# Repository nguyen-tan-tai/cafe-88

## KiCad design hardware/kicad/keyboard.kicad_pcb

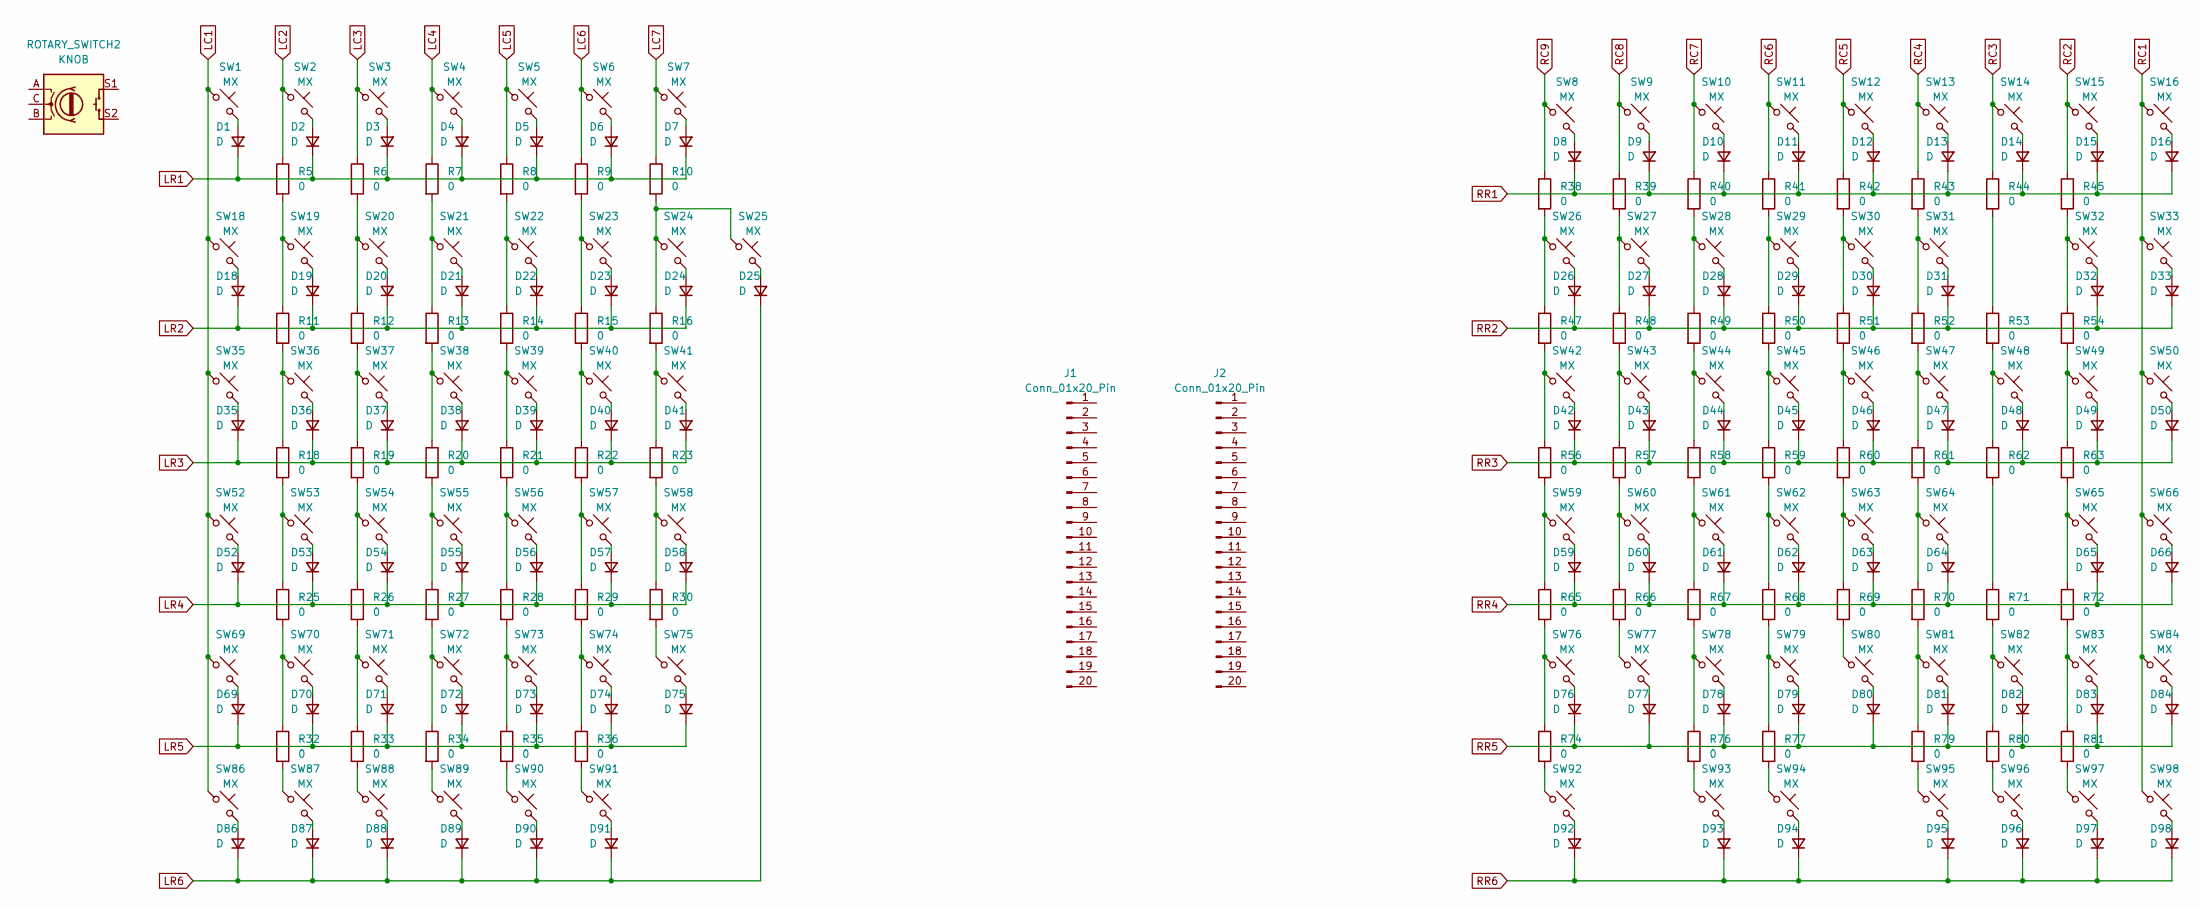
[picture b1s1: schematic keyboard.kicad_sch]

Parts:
D1, D2, D3, D4, D5, D6, D7, D8, D9, D10, D11, D12, D13, D14, D15, D16, D18, D19, D20, D21, D22, D23, D24, D25, D26, D27, D28, D29, D30, D31, D32, D33, D35, D36, D37, D38, D39, D40, D41, D42, D43, D44, D45, D46, D47, D48, D49, D50, D52, D53, D54, D55, D56, D57, D58, D59, D60, D61, D62, D63, D64, D65, D66, D69, D70, D71, D72, D73, D74, D75, D76, D77, D78, D79, D80, D81, D82, D83, D84, D86, D87, D88, D89, D90, D91, D92, D93, D94, D95, D96, D97, D98: D; D_MiniMELF_Handsoldering
J1, J2: Conn_01x20_Pin; PinHeader_1x20_P2.54mm_Vertical
R5, R6, R7, R8, R9, R10, R11, R12, R13, R14, R15, R16, R18, R19, R20, R21, R22, R23, R25, R26, R27, R28, R29, R30, R32, R33, R34, R35, R36, R38, R39, R40, R41, R42, R43, R44, R45, R47, R48, R49, R50, R51, R52, R53, R54, R56, R57, R58, R59, R60, R61, R62, R63, R65, R66, R67, R68, R69, R70, R71, R72, R74, R76, R77, R79, R80, R81: 0; R_2512_6332Metric_Pad1.40x3.35mm_HandSolder
ROTARY_SWITCH2: KNOB; RotaryEncoder_Alps_EC11E-Switch_Vertical_H20mm_CircularMoun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
SW1, SW2, SW3, SW4, SW5, SW6, SW7, SW8, SW9, SW10, SW11, SW12, SW13, SW14, SW15, SW16, SW18, SW19, SW20, SW21, SW22, SW23, SW24, SW25, SW26, SW27, SW28, SW29, SW30, SW31, SW32, SW33, SW35, SW36, SW37, SW38, SW39, SW40, SW41, SW42, SW43, SW44, SW45, SW46, SW47, SW48, SW49, SW50, SW52, SW53, SW54, SW55, SW56, SW57, SW58, SW59, SW60, SW61, SW62, SW63, SW64, SW65, SW66, SW69, SW70, SW71, SW72, SW73, SW74, SW75, SW76, SW77, SW78, SW79, SW80, SW81, SW82, SW83, SW84, SW86, SW87, SW88, SW89, SW90, SW91, SW92, SW93, SW94, SW95, SW96, SW97, SW98: MX; SW_Cherry_MX_1.00u_PCB

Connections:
LC1: SW1.1, SW18.1, SW35.1, SW52.1, SW69.1, SW86.1
LC2: R5.1, SW2.1
LC3: R6.1, SW3.1
LC4: R7.1, SW4.1
LC5: R8.1, SW5.1
LC6: R9.1, SW6.1
LC7: R10.1, SW7.1
LR1: D1.1 (K), D2.1 (K), D3.1 (K), D4.1 (K), D5.1 (K), D6.1 (K), D7.1 (K)
LR2: D18.1 (K), D19.1 (K), D20.1 (K), D21.1 (K), D22.1 (K), D23.1 (K), D24.1 (K)
LR3: D35.1 (K), D36.1 (K), D37.1 (K), D38.1 (K), D39.1 (K), D40.1 (K), D41.1 (K)
LR4: D52.1 (K), D53.1 (K), D54.1 (K), D55.1 (K), D56.1 (K), D57.1 (K), D58.1 (K)
LR5: D69.1 (K), D70.1 (K), D71.1 (K), D72.1 (K), D73.1 (K), D74.1 (K), D75.1 (K)
LR6: D25.1 (K), D86.1 (K), D87.1 (K), D88.1 (K), D89.1 (K), D90.1 (K), D91.1 (K)
unnamed: D1.2 (A), SW1.2
unnamed: D2.2 (A), SW2.2
unnamed: D3.2 (A), SW3.2
unnamed: D4.2 (A), SW4.2
unnamed: D5.2 (A), SW5.2
unnamed: D6.2 (A), SW6.2
unnamed: D7.2 (A), SW7.2
unnamed: D8.2 (A), SW8.2
unnamed: D9.2 (A), SW9.2
unnamed: D10.2 (A), SW10.2
unnamed: D11.2 (A), SW11.2
unnamed: D12.2 (A), SW12.2
unnamed: D13.2 (A), SW13.2
unnamed: D14.2 (A), SW14.2
unnamed: D15.2 (A), SW15.2
unnamed: D16.2 (A), SW16.2
unnamed: D18.2 (A), SW18.2
unnamed: D19.2 (A), SW19.2
unnamed: D20.2 (A), SW20.2
unnamed: D21.2 (A), SW21.2
unnamed: D22.2 (A), SW22.2
unnamed: D23.2 (A), SW23.2
unnamed: D24.2 (A), SW24.2
unnamed: D25.2 (A), SW25.2
unnamed: D26.2 (A), SW26.2
unnamed: D27.2 (A), SW27.2
unnamed: D28.2 (A), SW28.2
unnamed: D29.2 (A), SW29.2
unnamed: D30.2 (A), SW30.2
unnamed: D31.2 (A), SW31.2
unnamed: D32.2 (A), SW32.2
unnamed: D33.2 (A), SW33.2
unnamed: D35.2 (A), SW35.2
unnamed: D36.2 (A), SW36.2
unnamed: D37.2 (A), SW37.2
unnamed: D38.2 (A), SW38.2
unnamed: D39.2 (A), SW39.2
unnamed: D40.2 (A), SW40.2
unnamed: D41.2 (A), SW41.2
unnamed: D42.2 (A), SW42.2
unnamed: D43.2 (A), SW43.2
unnamed: D44.2 (A), SW44.2
unnamed: D45.2 (A), SW45.2
unnamed: D46.2 (A), SW46.2
unnamed: D47.2 (A), SW47.2
unnamed: D48.2 (A), SW48.2
unnamed: D49.2 (A), SW49.2
unnamed: D50.2 (A), SW50.2
unnamed: D52.2 (A), SW52.2
unnamed: D53.2 (A), SW53.2
unnamed: D54.2 (A), SW54.2
unnamed: D55.2 (A), SW55.2
unnamed: D56.2 (A), SW56.2
unnamed: D57.2 (A), SW57.2
unnamed: D58.2 (A), SW58.2
unnamed: D59.2 (A), SW59.2
unnamed: D60.2 (A), SW60.2
unnamed: D61.2 (A), SW61.2
unnamed: D62.2 (A), SW62.2
unnamed: D63.2 (A), SW63.2
unnamed: D64.2 (A), SW64.2
unnamed: D65.2 (A), SW65.2
unnamed: D66.2 (A), SW66.2
unnamed: D69.2 (A), SW69.2
unnamed: D70.2 (A), SW70.2
unnamed: D71.2 (A), SW71.2
unnamed: D72.2 (A), SW72.2
unnamed: D73.2 (A), SW73.2
unnamed: D74.2 (A), SW74.2
unnamed: D75.2 (A), SW75.2
unnamed: D76.2 (A), SW76.2
unnamed: D77.2 (A), SW77.2
unnamed: D78.2 (A), SW78.2
unnamed: D79.2 (A), SW79.2
unnamed: D80.2 (A), SW80.2
unnamed: D81.2 (A), SW81.2
unnamed: D82.2 (A), SW82.2
unnamed: D83.2 (A), SW83.2
unnamed: D84.2 (A), SW84.2
unnamed: D86.2 (A), SW86.2
unnamed: D87.2 (A), SW87.2
unnamed: D88.2 (A), SW88.2
unnamed: D89.2 (A), SW89.2
unnamed: D90.2 (A), SW90.2
unnamed: D91.2 (A), SW91.2
unnamed: D92.2 (A), SW92.2
unnamed: D93.2 (A), SW93.2
unnamed: D94.2 (A), SW94.2
unnamed: D95.2 (A), SW95.2
unnamed: D96.2 (A), SW96.2
unnamed: D97.2 (A), SW97.2
unnamed: D98.2 (A), SW98.2
unnamed: R10.2, R16.1, SW24.1, SW25.1
unnamed: R5.2, R11.1, SW19.1
unnamed: R11.2, R18.1, SW36.1
unnamed: R6.2, R12.1, SW20.1
unnamed: R12.2, R19.1, SW37.1
unnamed: R7.2, R13.1, SW21.1
unnamed: R13.2, R20.1, SW38.1
unnamed: R8.2, R14.1, SW22.1
unnamed: R14.2, R21.1, SW39.1
unnamed: R9.2, R15.1, SW23.1
unnamed: R15.2, R22.1, SW40.1
unnamed: R16.2, R23.1, SW41.1
unnamed: R18.2, R25.1, SW53.1
unnamed: R19.2, R26.1, SW54.1
unnamed: R20.2, R27.1, SW55.1
unnamed: R21.2, R28.1, SW56.1
unnamed: R22.2, R29.1, SW57.1
unnamed: R23.2, R30.1, SW58.1
unnamed: R25.2, R32.1, SW70.1
unnamed: R26.2, R33.1, SW71.1
unnamed: R27.2, R34.1, SW72.1
unnamed: R28.2, R35.1, SW73.1
unnamed: R29.2, R36.1, SW74.1
unnamed: R30.2, SW75.1
unnamed: R32.2, SW87.1
unnamed: R33.2, SW88.1
unnamed: R34.2, SW89.1
unnamed: R35.2, SW90.1
unnamed: R36.2, SW91.1
unnamed: R38.2, R47.1, SW26.1
unnamed: R39.2, R48.1, SW27.1
unnamed: R40.2, R49.1, SW28.1
unnamed: R41.2, R50.1, SW29.1
unnamed: R42.2, R51.1, SW30.1
unnamed: R43.2, R52.1, SW31.1
unnamed: R44.2, R53.1
unnamed: R45.2, R54.1, SW32.1
unnamed: R47.2, R56.1, SW42.1
unnamed: R48.2, R57.1, SW43.1
unnamed: R49.2, R58.1, SW44.1
unnamed: R50.2, R59.1, SW45.1
unnamed: R51.2, R60.1, SW46.1
unnamed: R52.2, R61.1, SW47.1
unnamed: R53.2, R62.1, SW48.1
unnamed: R54.2, R63.1, SW49.1
unnamed: R56.2, R65.1, SW59.1
unnamed: R57.2, R66.1, SW60.1
unnamed: R58.2, R67.1, SW61.1
unnamed: R59.2, R68.1, SW62.1
unnamed: R60.2, R69.1, SW63.1
unnamed: R61.2, R70.1, SW64.1
unnamed: R62.2, R71.1
unnamed: R63.2, R72.1, SW65.1
unnamed: R65.2, R74.1, SW76.1
unnamed: R66.2, SW77.1
unnamed: R67.2, R76.1, SW78.1
unnamed: R68.2, R77.1, SW79.1
unnamed: R69.2, SW80.1
unnamed: R70.2, R79.1, SW81.1
unnamed: R71.2, R80.1, SW82.1
unnamed: R72.2, R81.1, SW83.1
unnamed: R74.2, SW92.1
unnamed: R76.2, SW93.1
unnamed: R77.2, SW94.1
unnamed: R79.2, SW95.1
unnamed: R80.2, SW96.1
unnamed: R81.2, SW97.1
RC1: SW16.1, SW33.1, SW50.1, SW66.1, SW84.1, SW98.1
RC2: R45.1, SW15.1
RC3: R44.1, SW14.1
RC4: R43.1, SW13.1
RC5: R42.1, SW12.1
RC6: R41.1, SW11.1
RC7: R40.1, SW10.1
RC8: R39.1, SW9.1
RC9: R38.1, SW8.1
RR1: D8.1 (K), D9.1 (K), D10.1 (K), D11.1 (K), D12.1 (K), D13.1 (K), D14.1 (K), D15.1 (K), D16.1 (K)
RR2: D26.1 (K), D27.1 (K), D28.1 (K), D29.1 (K), D30.1 (K), D31.1 (K), D32.1 (K), D33.1 (K)
RR3: D42.1 (K), D43.1 (K), D44.1 (K), D45.1 (K), D46.1 (K), D47.1 (K), D48.1 (K), D49.1 (K), D50.1 (K)
RR4: D59.1 (K), D60.1 (K), D61.1 (K), D62.1 (K), D63.1 (K), D64.1 (K), D65.1 (K), D66.1 (K)
RR5: D76.1 (K), D77.1 (K), D78.1 (K), D79.1 (K), D80.1 (K), D81.1 (K), D82.1 (K), D83.1 (K), D84.1 (K)
RR6: D92.1 (K), D93.1 (K), D94.1 (K), D95.1 (K), D96.1 (K), D97.1 (K), D98.1 (K)

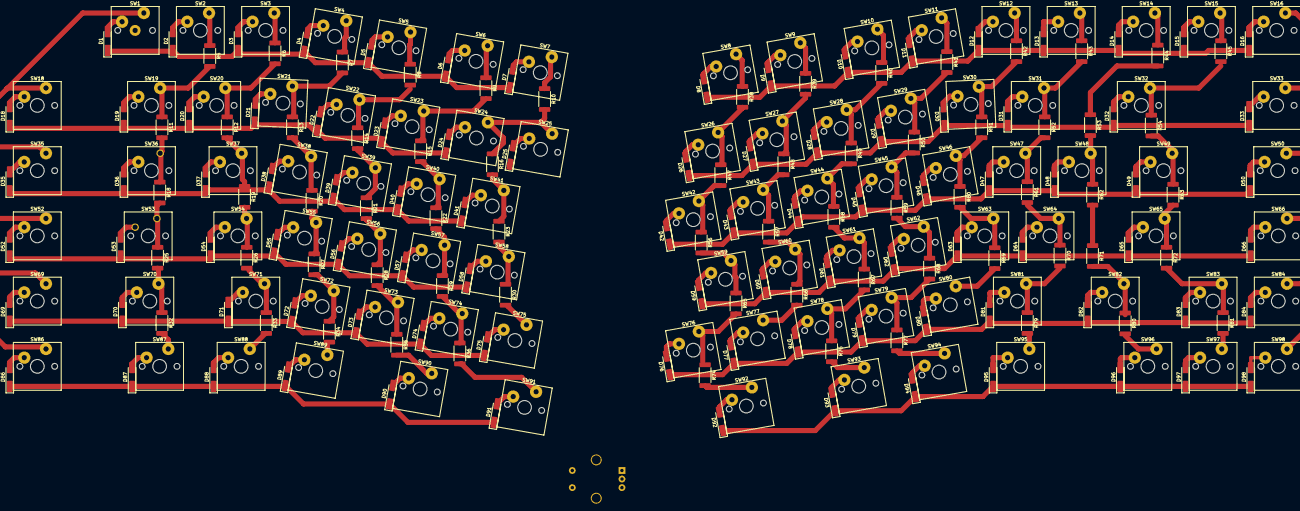
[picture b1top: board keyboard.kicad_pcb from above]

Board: 2 copper layers, 252 parts (1 on the bottom side), 187 nets.

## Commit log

2023-07-29 Init
2023-07-30 misc
